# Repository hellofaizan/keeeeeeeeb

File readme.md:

# keeeeeeep
Custom designed and developed Split Keyboad

# Making

### Making
- Designed the 16 x 5 matrix for the main QWERTY and numbers and special keys

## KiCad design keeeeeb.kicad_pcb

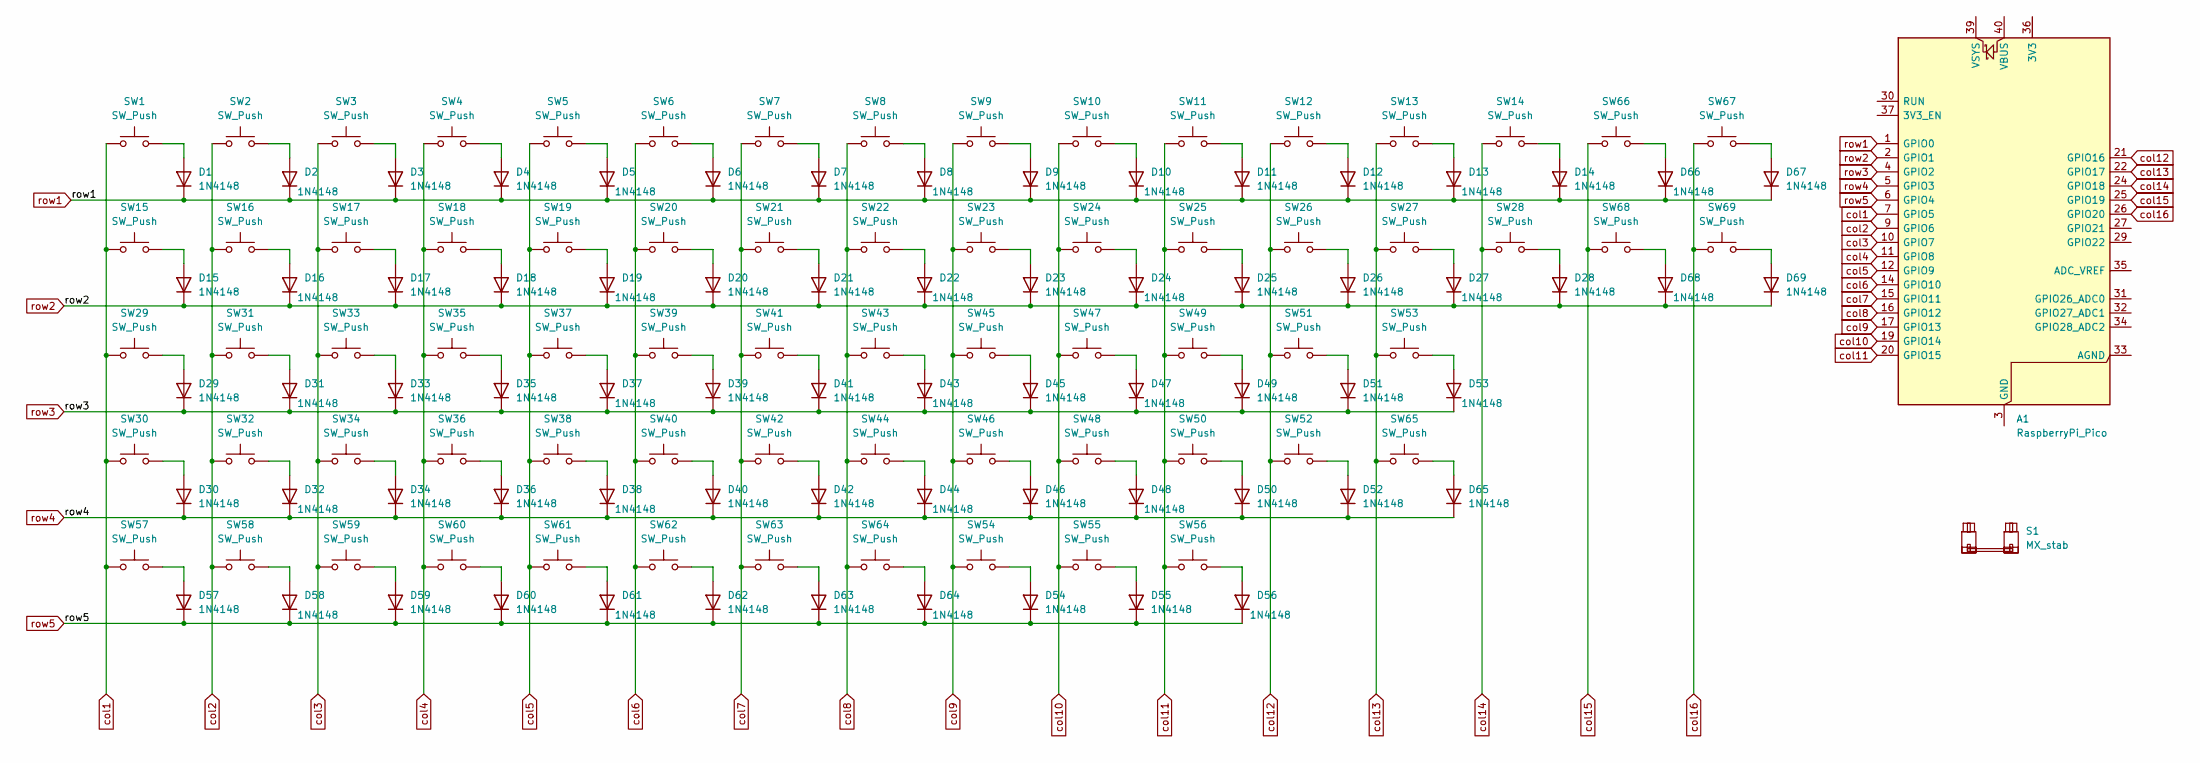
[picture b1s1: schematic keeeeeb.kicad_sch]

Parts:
A1: RaspberryPi_Pico; RaspberryPi_Pico_Common_Unspecified
D1, D2, D3, D4, D5, D6, D7, D8, D9, D10, D11, D12, D13, D14, D15, D16, D17, D18, D19, D20, D21, D22, D23, D24, D25, D26, D27, D28, D29, D30, D31, D32, D33, D34, D35, D36, D37, D38, D39, D40, D41, D42, D43, D44, D45, D46, D47, D48, D49, D50, D51, D52, D53, D54, D55, D56, D57, D58, D59, D60, D61, D62, D63, D64, D65, D66, D67, D68, D69: 1N4148; D_DO-35_SOD27_P7.62mm_Horizontal
S1: MX_stab; STAB_MX_P_6.25u
SW1, SW2, SW3, SW4, SW5, SW6, SW7, SW8, SW9, SW10, SW11, SW12, SW13, SW15, SW16, SW18, SW19, SW20, SW21, SW22, SW23, SW24, SW25, SW26, SW27, SW28, SW29, SW31, SW32, SW34, SW35, SW36, SW37, SW38, SW39, SW40, SW41, SW42, SW43, SW44, SW47, SW48, SW49, SW50, SW51, SW52, SW53, SW54, SW55, SW56, SW58, SW67, SW68, SW69: SW_Push; SW_Cherry_MX_1.00u_PCB
SW14: SW_Push; SW_Cherry_MX_2.00u_PCB
SW17, SW30: SW_Push; SW_Cherry_MX_1.50u_PCB
SW33: SW_Push; SW_Cherry_MX_1.75u_PCB
SW45, SW46: SW_Push; SW_Cherry_MX_2.25u_PCB
SW57: SW_Push; SW_Cherry_MX_2.75u_PCB
SW59, SW60, SW61, SW63, SW64, SW65, SW66: SW_Push; SW_Cherry_MX_1.25u_PCB
SW62: SW_Push; SW_Cherry_MX_6.25u_PCB

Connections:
unnamed: A1.3 (GND), A1.8 (GND), A1.13 (GND), A1.18 (GND), A1.23 (GND), A1.28 (GND), A1.38 (GND)
unnamed: D1.2 (A), SW1.2
unnamed: D2.2 (A), SW2.2
unnamed: D3.2 (A), SW3.2
unnamed: D4.2 (A), SW4.2
unnamed: D5.2 (A), SW5.2
unnamed: D6.2 (A), SW6.2
unnamed: D7.2 (A), SW7.2
unnamed: D8.2 (A), SW8.2
unnamed: D9.2 (A), SW9.2
unnamed: D10.2 (A), SW10.2
unnamed: D11.2 (A), SW11.2
unnamed: D12.2 (A), SW12.2
unnamed: D13.2 (A), SW13.2
unnamed: D14.2 (A), SW14.2
unnamed: D15.2 (A), SW15.2
unnamed: D16.2 (A), SW16.2
unnamed: D17.2 (A), SW17.2
unnamed: D18.2 (A), SW18.2
unnamed: D19.2 (A), SW19.2
unnamed: D20.2 (A), SW20.2
unnamed: D21.2 (A), SW21.2
unnamed: D22.2 (A), SW22.2
unnamed: D23.2 (A), SW23.2
unnamed: D24.2 (A), SW24.2
unnamed: D25.2 (A), SW25.2
unnamed: D26.2 (A), SW26.2
unnamed: D27.2 (A), SW27.2
unnamed: D28.2 (A), SW28.2
unnamed: D29.2 (A), SW29.2
unnamed: D30.2 (A), SW30.2
unnamed: D31.2 (A), SW31.2
unnamed: D32.2 (A), SW32.2
unnamed: D33.2 (A), SW33.2
unnamed: D34.2 (A), SW34.2
unnamed: D35.2 (A), SW35.2
unnamed: D36.2 (A), SW36.2
unnamed: D37.2 (A), SW37.2
unnamed: D38.2 (A), SW38.2
unnamed: D39.2 (A), SW39.2
unnamed: D40.2 (A), SW40.2
unnamed: D41.2 (A), SW41.2
unnamed: D42.2 (A), SW42.2
unnamed: D43.2 (A), SW43.2
unnamed: D44.2 (A), SW44.2
unnamed: D45.2 (A), SW45.2
unnamed: D46.2 (A), SW46.2
unnamed: D47.2 (A), SW47.2
unnamed: D48.2 (A), SW48.2
unnamed: D49.2 (A), SW49.2
unnamed: D50.2 (A), SW50.2
unnamed: D51.2 (A), SW51.2
unnamed: D52.2 (A), SW52.2
unnamed: D53.2 (A), SW53.2
unnamed: D54.2 (A), SW54.2
unnamed: D55.2 (A), SW55.2
unnamed: D56.2 (A), SW56.2
unnamed: D57.2 (A), SW57.2
unnamed: D58.2 (A), SW58.2
unnamed: D59.2 (A), SW59.2
unnamed: D60.2 (A), SW60.2
unnamed: D61.2 (A), SW61.2
unnamed: D62.2 (A), SW62.2
unnamed: D63.2 (A), SW63.2
unnamed: D64.2 (A), SW64.2
unnamed: D65.2 (A), SW65.2
unnamed: D66.2 (A), SW66.2
unnamed: D67.2 (A), SW67.2
unnamed: D68.2 (A), SW68.2
unnamed: D69.2 (A), SW69.2
col1: A1.7 (GPIO5), SW1.1, SW15.1, SW29.1, SW30.1, SW57.1
col2: A1.9 (GPIO6), SW2.1, SW16.1, SW31.1, SW32.1, SW58.1
col3: A1.10 (GPIO7), SW3.1, SW17.1, SW33.1, SW34.1, SW59.1
col4: A1.11 (GPIO8), SW4.1, SW18.1, SW35.1, SW36.1, SW60.1
col5: A1.12 (GPIO9), SW5.1, SW19.1, SW37.1, SW38.1, SW61.1
col6: A1.14 (GPIO10), SW6.1, SW20.1, SW39.1, SW40.1, SW62.1
col7: A1.15 (GPIO11), SW7.1, SW21.1, SW41.1, SW42.1, SW63.1
col8: A1.16 (GPIO12), SW8.1, SW22.1, SW43.1, SW44.1, SW64.1
col9: A1.17 (GPIO13), SW9.1, SW23.1, SW45.1, SW46.1, SW54.1
col10: A1.19 (GPIO14), SW10.1, SW24.1, SW47.1, SW48.1, SW55.1
col11: A1.20 (GPIO15), SW11.1, SW25.1, SW49.1, SW50.1, SW56.1
col12: A1.21 (GPIO16), SW12.1, SW26.1, SW51.1, SW52.1
col13: A1.22 (GPIO17), SW13.1, SW27.1, SW53.1, SW65.1
col14: A1.24 (GPIO18), SW14.1, SW28.1
col15: A1.25 (GPIO19), SW66.1, SW68.1
col16: A1.26 (GPIO20), SW67.1, SW69.1
row1: A1.1 (GPIO0), D1.1 (K), D2.1 (K), D3.1 (K), D4.1 (K), D5.1 (K), D6.1 (K), D7.1 (K), D8.1 (K), D9.1 (K), D10.1 (K), D11.1 (K), D12.1 (K), D13.1 (K), D14.1 (K), D66.1 (K), D67.1 (K)
row2: A1.2 (GPIO1), D15.1 (K), D16.1 (K), D17.1 (K), D18.1 (K), D19.1 (K), D20.1 (K), D21.1 (K), D22.1 (K), D23.1 (K), D24.1 (K), D25.1 (K), D26.1 (K), D27.1 (K), D28.1 (K), D68.1 (K), D69.1 (K)
row3: A1.4 (GPIO2), D29.1 (K), D31.1 (K), D33.1 (K), D35.1 (K), D37.1 (K), D39.1 (K), D41.1 (K), D43.1 (K), D45.1 (K), D47.1 (K), D49.1 (K), D51.1 (K), D53.1 (K)
row4: A1.5 (GPIO3), D30.1 (K), D32.1 (K), D34.1 (K), D36.1 (K), D38.1 (K), D40.1 (K), D42.1 (K), D44.1 (K), D46.1 (K), D48.1 (K), D50.1 (K), D52.1 (K), D65.1 (K)
row5: A1.6 (GPIO4), D54.1 (K), D55.1 (K), D56.1 (K), D57.1 (K), D58.1 (K), D59.1 (K), D60.1 (K), D61.1 (K), D62.1 (K), D63.1 (K), D64.1 (K)

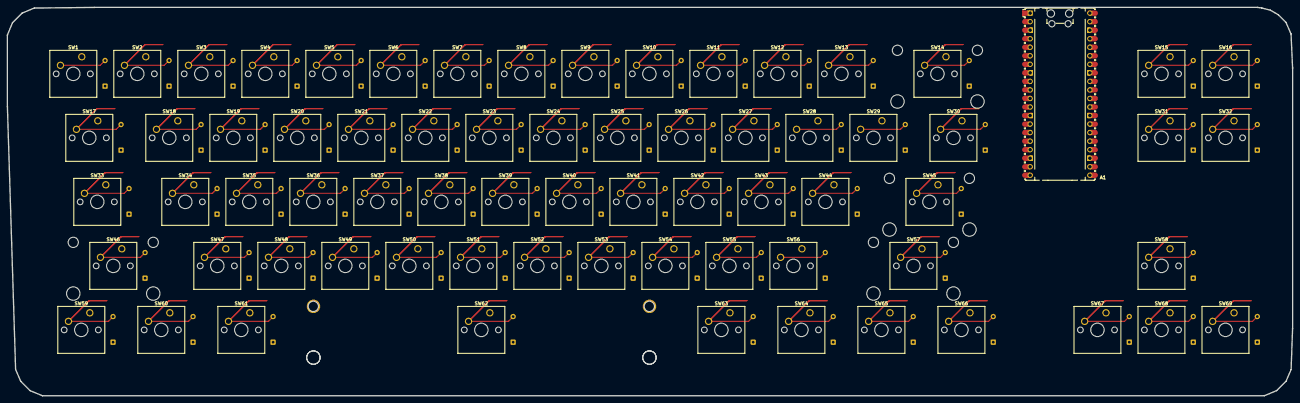
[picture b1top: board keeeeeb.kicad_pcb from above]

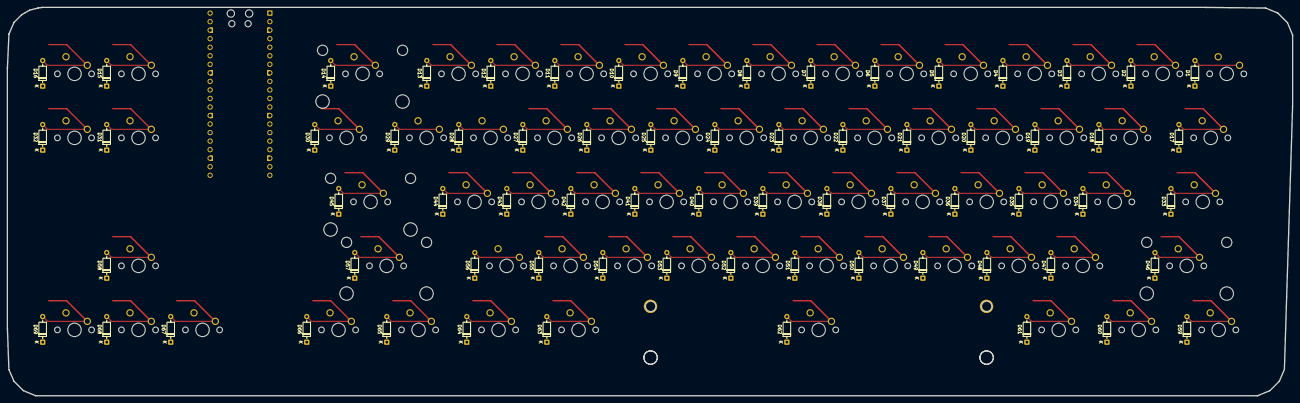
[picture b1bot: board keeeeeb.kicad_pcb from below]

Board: 2 copper layers, 382.5 x 115.6 mm, 140 parts (69 on the bottom side), 91 nets.

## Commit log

2026-06-18 basic pcb setup done, no wiring, no leds, no knobs and no led
2026-06-18 added readme file
2026-06-18 ignored some files from git
2026-06-18 removed some gitignored files
2026-06-18 removed auto saved file txt
2026-06-18 Update keyboard matrix design details in README
